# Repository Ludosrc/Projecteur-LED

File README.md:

# Projecteur-LED
Projet 1A Projecteur LED

Vous pouvez trouver dans le fichier Rapport Projecteur LED Asservi toute la conception du projecteur LED ainsi que les problèmes rencontrés.
À savoir que le projecteur n'est pas fonctionnel pour de multiples raisons qui sont détaillés dans le compte rendu.

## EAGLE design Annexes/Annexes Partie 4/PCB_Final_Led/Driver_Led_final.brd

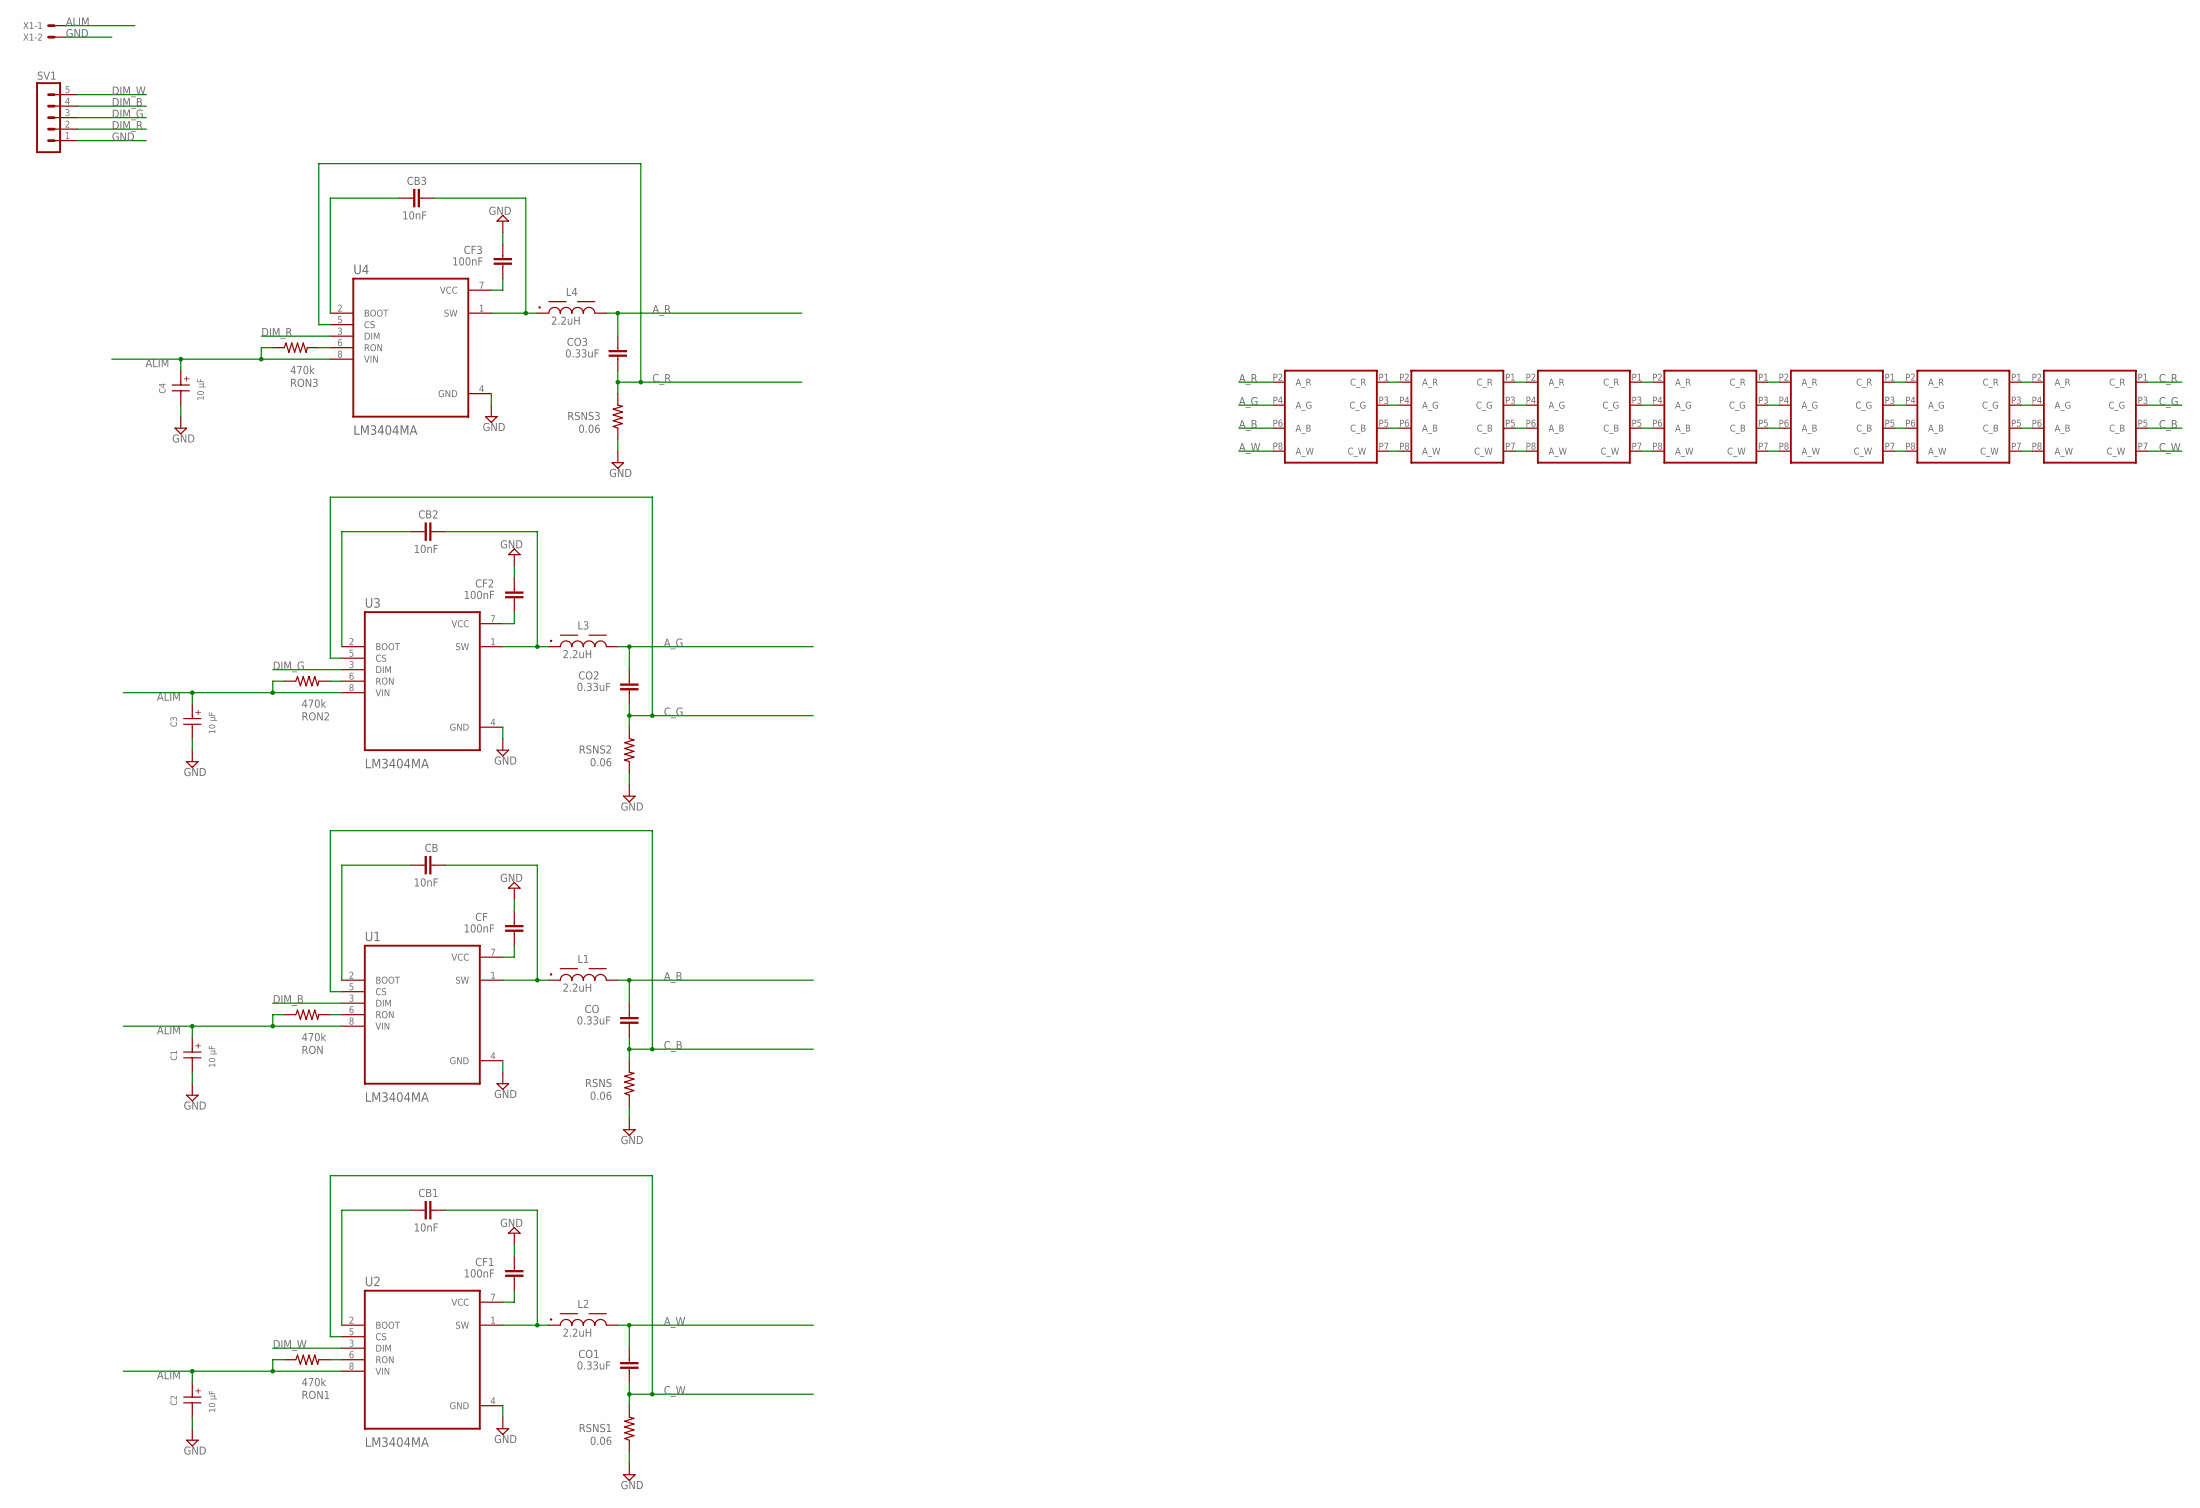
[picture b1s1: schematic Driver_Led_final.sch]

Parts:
C1, C2, C3, C4: 10 µF; WCAP-ASLL_4X5.5(DXL)
CB, CB1, CB2, CB3: 10nF; C0603
CF, CF1, CF2, CF3: 100nF; C0603
CO, CO1, CO2, CO3: 0.33uF; C0603
L1, L2, L3, L4: 2.2uH; WE-PDA_1260
RON, RON1, RON2, RON3: 470k; R0603
RSNS, RSNS1, RSNS2, RSNS3: 0.06; R0603
SV1: MA05-1
U1, U2, U3, U4: LM3404MA; SOIC127P599X175-8N
U$1, U$2, U$3, U$4, U$5, U$6, U$7: LE_RTDUW_S2WM_DEVICE; LE_RTDUW_S2WM_FOOTPRINT
X1: 22-23-2021

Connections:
ALIM: C1.1 (+), C2.1 (+), C3.1 (+), C4.1 (+), RON.1, RON1.1, RON2.1, RON3.1, U1.8 (VIN), U2.8 (VIN), U3.8 (VIN), U4.8 (VIN), X1.1
A_B: CO.2, L1.2, U$1.P6 (A_B)
A_G: CO2.2, L3.2, U$1.P4 (A_G)
A_R: CO3.2, L4.2, U$1.P2 (A_R)
A_W: CO1.2, L2.2, U$1.P8 (A_W)
C_B: CO.1, RSNS.2, U1.5 (CS), U$7.P5 (C_B)
C_G: CO2.1, RSNS2.2, U3.5 (CS), U$7.P3 (C_G)
C_R: CO3.1, RSNS3.2, U4.5 (CS), U$7.P1 (C_R)
C_W: CO1.1, RSNS1.2, U2.5 (CS), U$7.P7 (C_W)
DIM_B: SV1.4, U1.3 (DIM)
DIM_G: SV1.3, U3.3 (DIM)
DIM_R: SV1.2, U4.3 (DIM)
DIM_W: SV1.5, U2.3 (DIM)
GND: C1.2 (-), C2.2 (-), C3.2 (-), C4.2 (-), CF.1, CF1.1, CF2.1, CF3.1, RSNS.1, RSNS1.1, RSNS2.1, RSNS3.1, SV1.1, U1.4 (GND), U2.4 (GND), U3.4 (GND), U4.4 (GND), X1.2
unnamed: RON.2, U1.6 (RON)
unnamed: CB1.1, U2.2 (BOOT)
unnamed: CF.2, U1.7 (VCC)
unnamed: CB.1, U1.2 (BOOT)
unnamed: CB.2, L1.1, U1.1 (SW)
unnamed: CB1.2, L2.1, U2.1 (SW)
unnamed: CF1.2, U2.7 (VCC)
unnamed: RON1.2, U2.6 (RON)
unnamed: CB2.1, U3.2 (BOOT)
unnamed: CB2.2, L3.1, U3.1 (SW)
unnamed: CF2.2, U3.7 (VCC)
unnamed: RON2.2, U3.6 (RON)
unnamed: CB3.1, U4.2 (BOOT)
unnamed: CB3.2, L4.1, U4.1 (SW)
unnamed: CF3.2, U4.7 (VCC)
unnamed: RON3.2, U4.6 (RON)
unnamed: U$1.P1 (C_R), U$2.P2 (A_R)
unnamed: U$1.P3 (C_G), U$2.P4 (A_G)
unnamed: U$1.P5 (C_B), U$2.P6 (A_B)
unnamed: U$1.P7 (C_W), U$2.P8 (A_W)
unnamed: U$2.P1 (C_R), U$3.P2 (A_R)
unnamed: U$2.P3 (C_G), U$3.P4 (A_G)
unnamed: U$2.P5 (C_B), U$3.P6 (A_B)
unnamed: U$2.P7 (C_W), U$3.P8 (A_W)
unnamed: U$3.P7 (C_W), U$4.P8 (A_W)
unnamed: U$3.P5 (C_B), U$4.P6 (A_B)
unnamed: U$3.P3 (C_G), U$4.P4 (A_G)
unnamed: U$3.P1 (C_R), U$4.P2 (A_R)
unnamed: U$4.P1 (C_R), U$5.P2 (A_R)
unnamed: U$4.P3 (C_G), U$5.P4 (A_G)
unnamed: U$4.P5 (C_B), U$5.P6 (A_B)
unnamed: U$4.P7 (C_W), U$5.P8 (A_W)
unnamed: U$5.P1 (C_R), U$6.P2 (A_R)
unnamed: U$5.P3 (C_G), U$6.P4 (A_G)
unnamed: U$5.P5 (C_B), U$6.P6 (A_B)
unnamed: U$5.P7 (C_W), U$6.P8 (A_W)
unnamed: U$6.P1 (C_R), U$7.P2 (A_R)
unnamed: U$6.P3 (C_G), U$7.P4 (A_G)
unnamed: U$6.P5 (C_B), U$7.P6 (A_B)
unnamed: U$6.P7 (C_W), U$7.P8 (A_W)

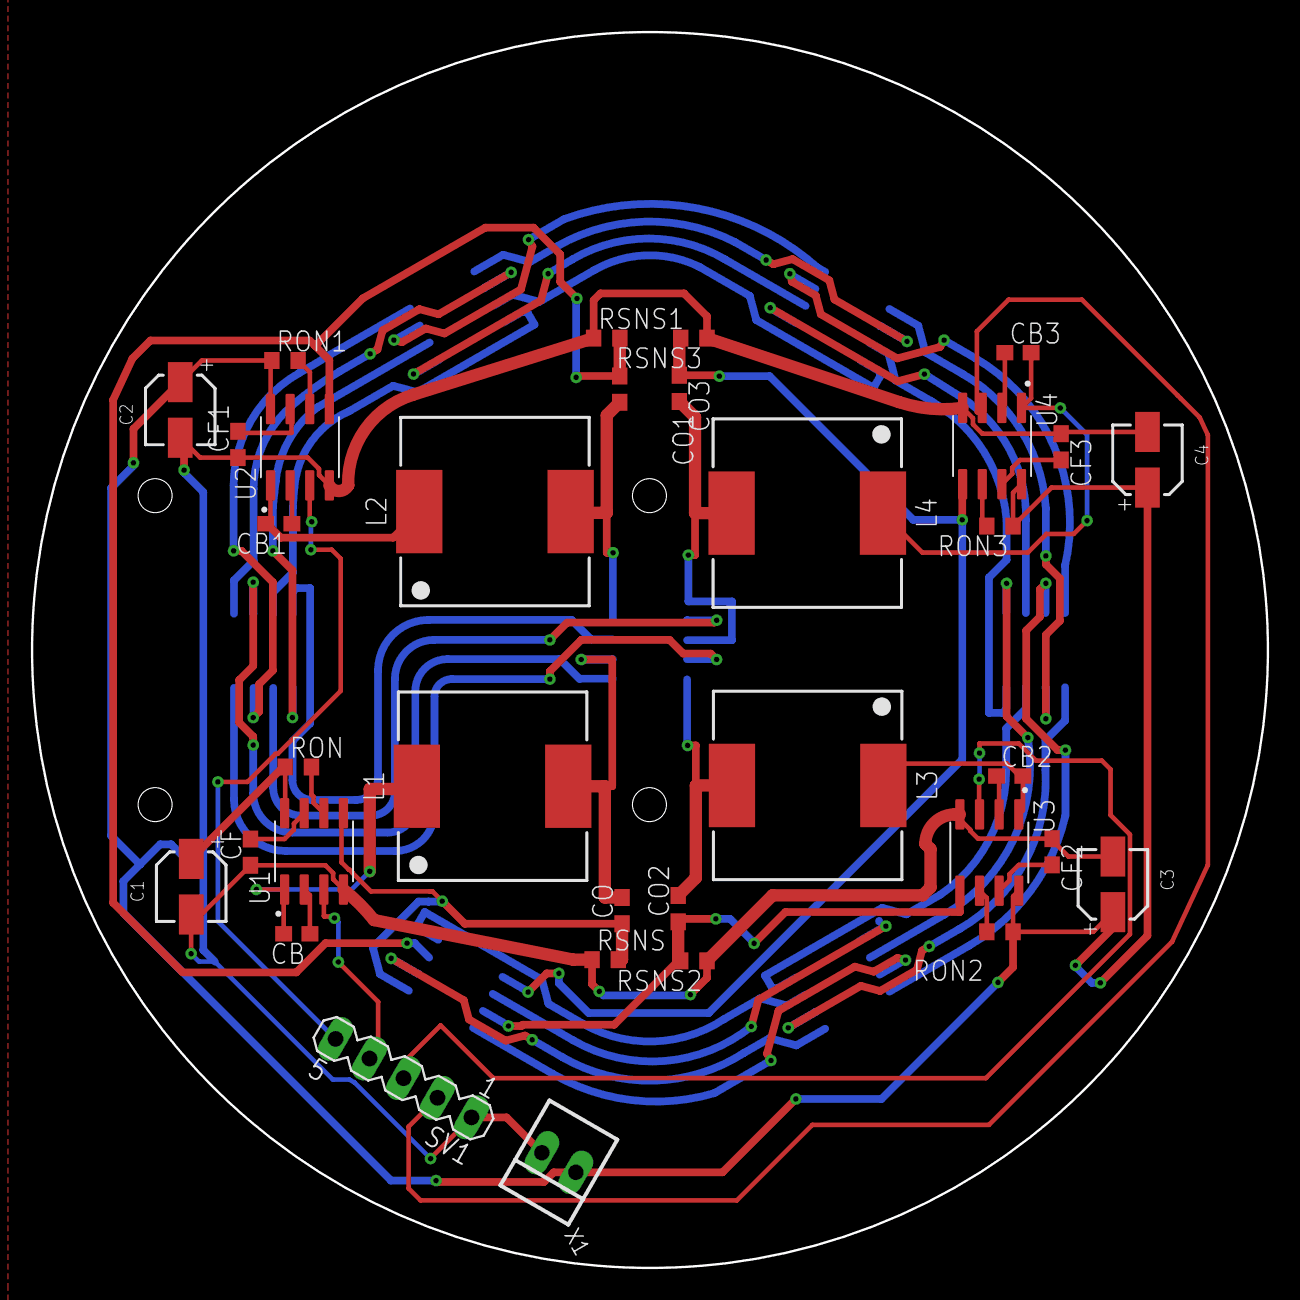
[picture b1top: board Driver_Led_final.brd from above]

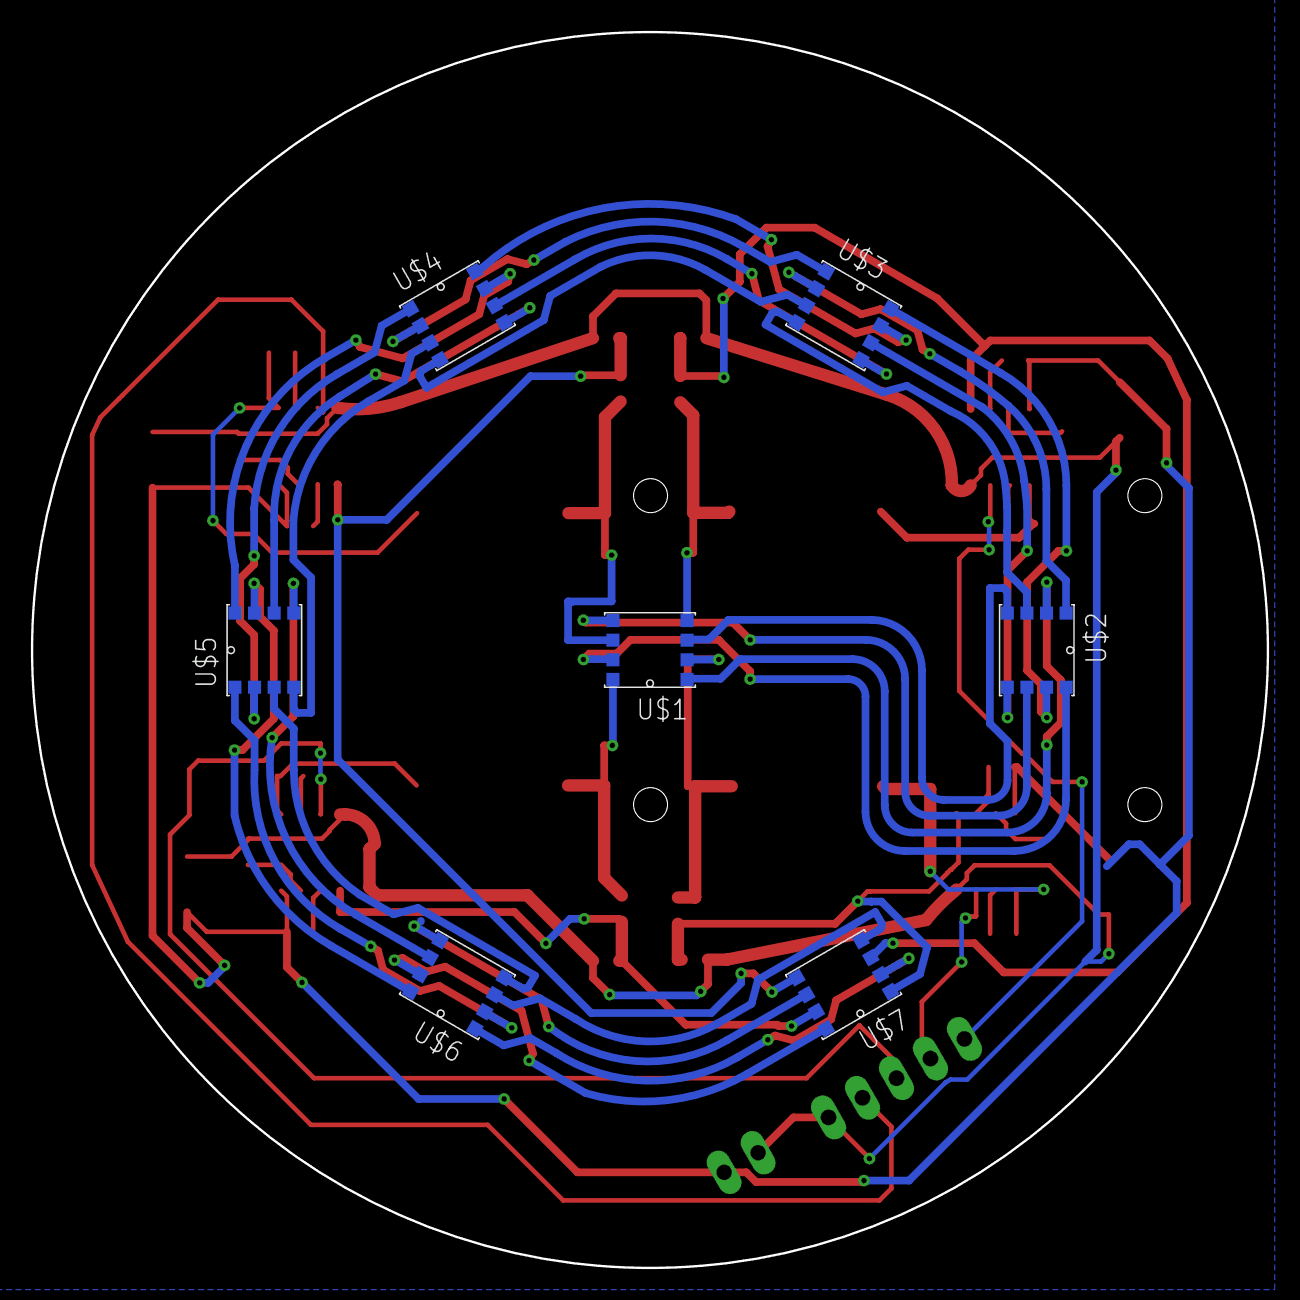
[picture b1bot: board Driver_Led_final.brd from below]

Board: 2 copper layers, 80.0 x 80.0 mm, 41 parts (7 on the bottom side), 54 nets.

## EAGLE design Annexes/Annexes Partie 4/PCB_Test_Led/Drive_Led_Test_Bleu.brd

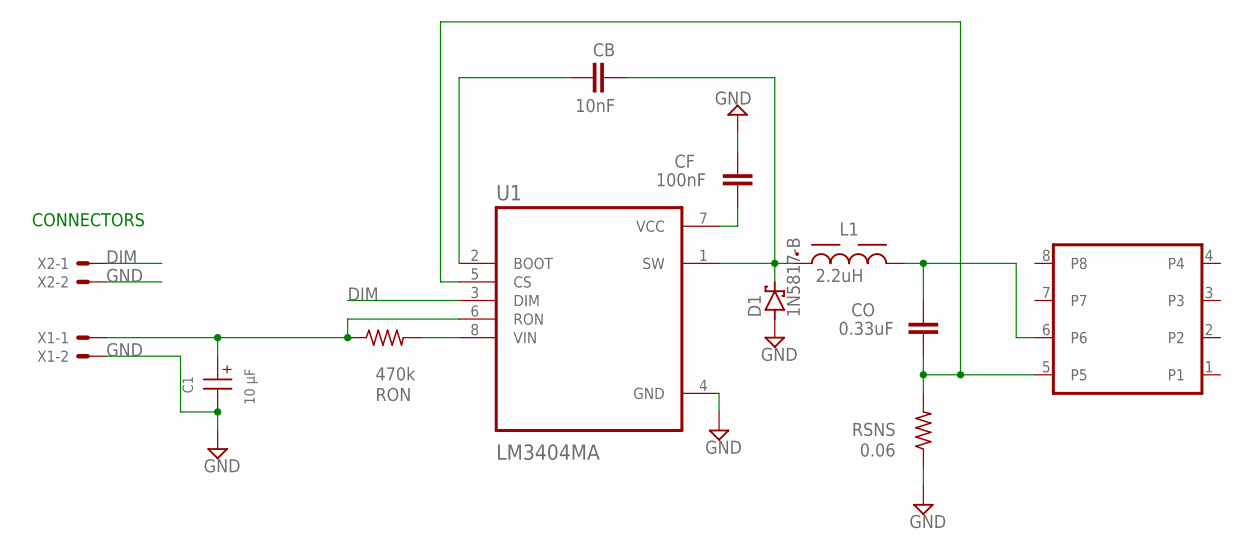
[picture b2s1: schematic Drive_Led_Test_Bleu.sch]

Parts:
C1: 10 µF; WCAP-ASLL_4X5.5(DXL)
CB: 10nF; C0603
CF: 100nF; C0603
CO: 0.33uF; C0603
D1: 1N5817-B; DO41-7.6
L1: 2.2uH; WE-PDA_1260
RON: 470k; R0603
RSNS: 0.06; R0603
U1: LM3404MA; SOIC127P599X175-8N
U$1: LE_RTDUW_S2WM_DEVICE; LE_RTDUW_S2WM_FOOTPRINT
X1, X2: 22-23-2021

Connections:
DIM: U1.3 (DIM), X2.1
GND: C1.2 (-), CF.1, D1.A, RSNS.1, U1.4 (GND), X1.2, X2.2
unnamed: RON.2, U1.8 (VIN)
unnamed: C1.1 (+), RON.1, U1.6 (RON), X1.1
unnamed: CF.2, U1.7 (VCC)
unnamed: CB.1, U1.2 (BOOT)
unnamed: CB.2, D1.C, L1.1, U1.1 (SW)
unnamed: CO.1, RSNS.2, U1.5 (CS), U$1.5
unnamed: CO.2, L1.2, U$1.6
P1: U$1.1
P2: U$1.2

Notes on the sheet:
CONNECTORS

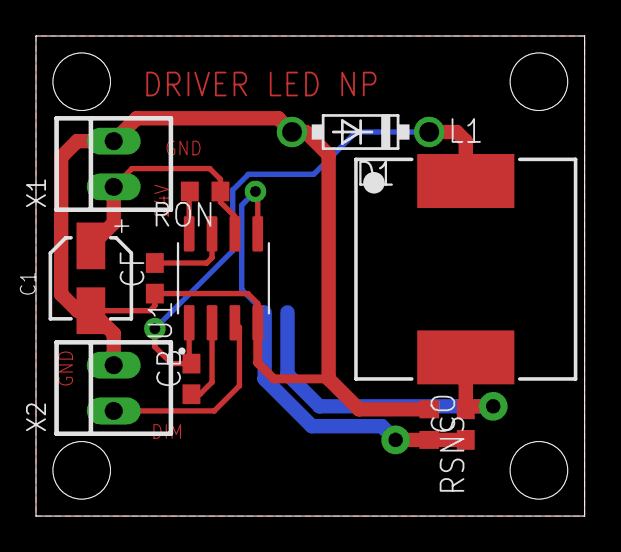
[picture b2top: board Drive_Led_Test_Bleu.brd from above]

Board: 2 copper layers, 30.5 x 26.7 mm, 12 parts (1 on the bottom side), 9 nets.

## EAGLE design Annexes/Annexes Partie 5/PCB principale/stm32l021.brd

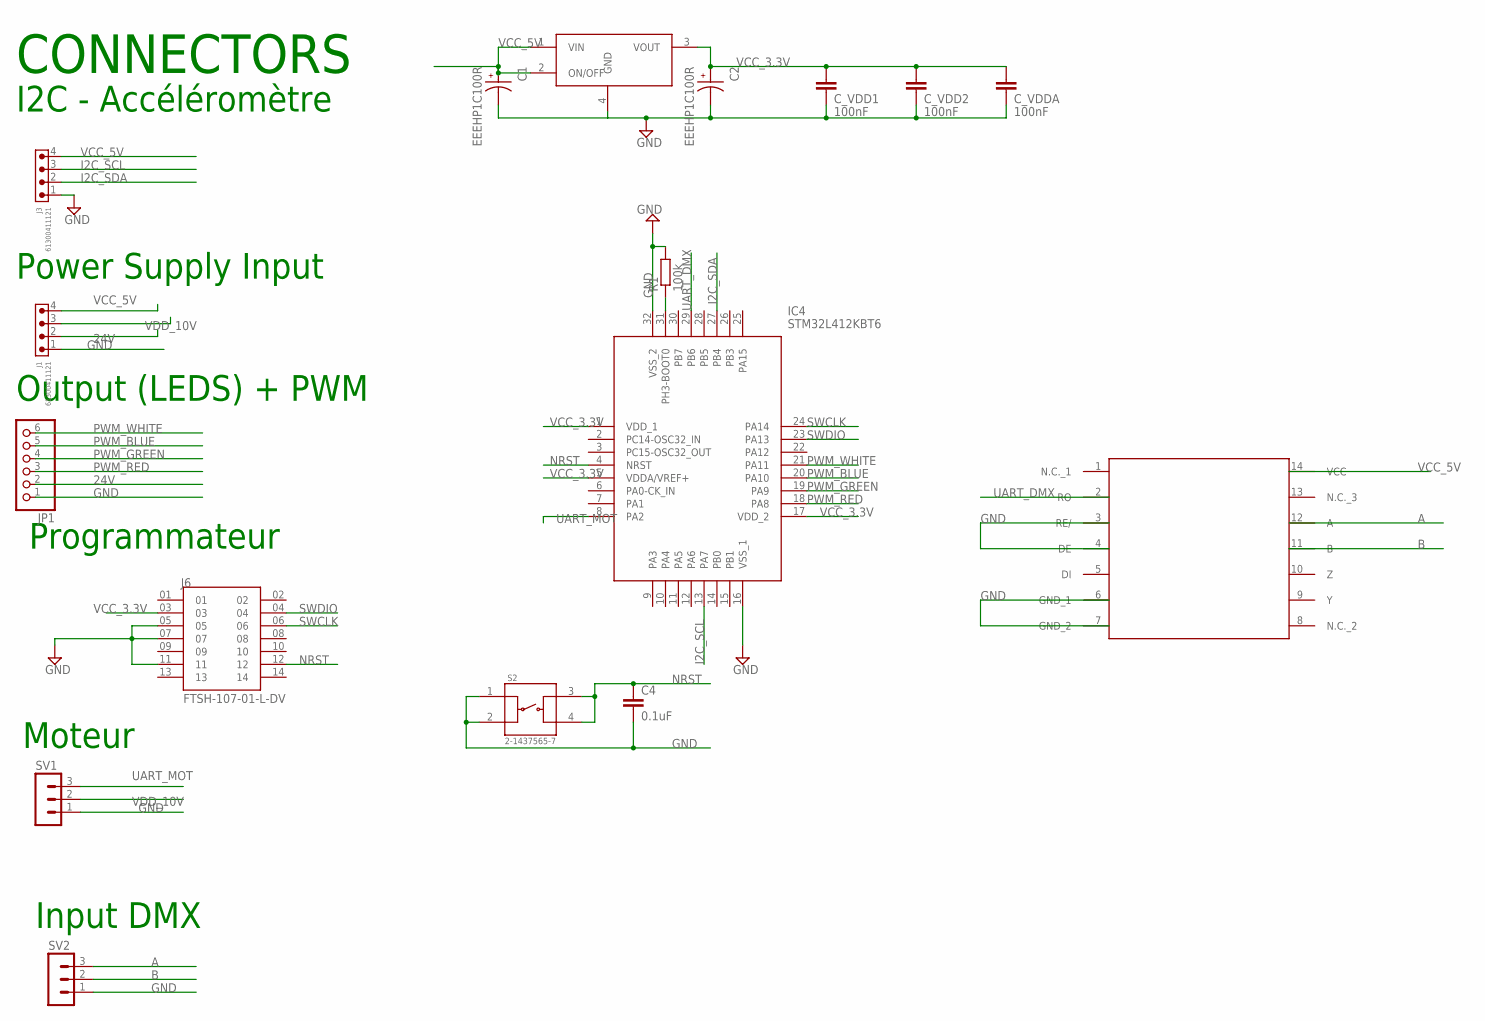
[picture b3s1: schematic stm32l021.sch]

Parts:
C1, C2: EEEHP1C100R; CAP_EEEHP1C100R
C4: 0.1uF; C0603
C_VDD1, C_VDD2: 100nF; C0603
C_VDDA: 100nF; C0603
IC4: STM32L412KBT6; QFP80P900X900X160-32N
J1, J3: 61300411121
J6: FTSH-107-01-L-DV; SAMTEC_FTSH-107-01-L-DV
JP1: PINHD-1X6; 1X06
R1: 100k; R0603
S2: 2-1437565-7; SW_2-1437565-7
SV1, SV2: MA03-1
U1: SOIC127P600X175-14N
U$1: NCV33375ST3.3T3G; VREG_NCP1117STAT3G

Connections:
24V: J1.2, JP1.2
A: SV2.3, U1.12 (A)
B: SV2.2, U1.11 (B)
GND: C1.2, C2.2, C4.2, C_VDD1.2, C_VDD2.2, C_VDDA.2, IC4.16 (VSS_1), IC4.32 (VSS_2), J1.1, J3.1, J6.05, J6.07, J6.11, JP1.1, R1.2, S2.1, S2.2, SV1.1, SV2.1, U1.3 (RE/), U1.4 (DE), U1.6 (GND_1), U1.7 (GND_2), U$1.4 (GND)
I2C_SCL: IC4.13 (PA7), J3.3
I2C_SDA: IC4.27 (PB4), J3.2
unnamed: IC4.31 (PH3-BOOT0), R1.1
NRST: C4.1, IC4.4 (NRST), J6.12, S2.3, S2.4
PWM_BLUE: IC4.20 (PA10), JP1.5
PWM_GREEN: IC4.19 (PA9), JP1.4
PWM_RED: IC4.18 (PA8), JP1.3
PWM_WHITE: IC4.21 (PA11), JP1.6
SWCLK: IC4.24 (PA14), J6.06
SWDIO: IC4.23 (PA13), J6.04
UART_DMX: IC4.29 (PB6), U1.2 (RO)
UART_MOT: IC4.8 (PA2), SV1.3
VCC_3.3V: C2.1, C_VDD1.1, C_VDD2.1, C_VDDA.1, IC4.1 (VDD_1), IC4.5 (VDDA/VREF+), IC4.17 (VDD_2), J6.03, U$1.3 (VOUT)
VCC_5V: C1.1, J1.4, J3.4, U1.14 (VCC), U$1.1 (VIN), U$1.2 (ON/OFF)
VDD_10V: J1.3, SV1.2

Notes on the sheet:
CONNECTORS
I2C - Accéléromètre
Power Supply Input
Programmateur
Output (LEDS) + PWM
Moteur
Input DMX

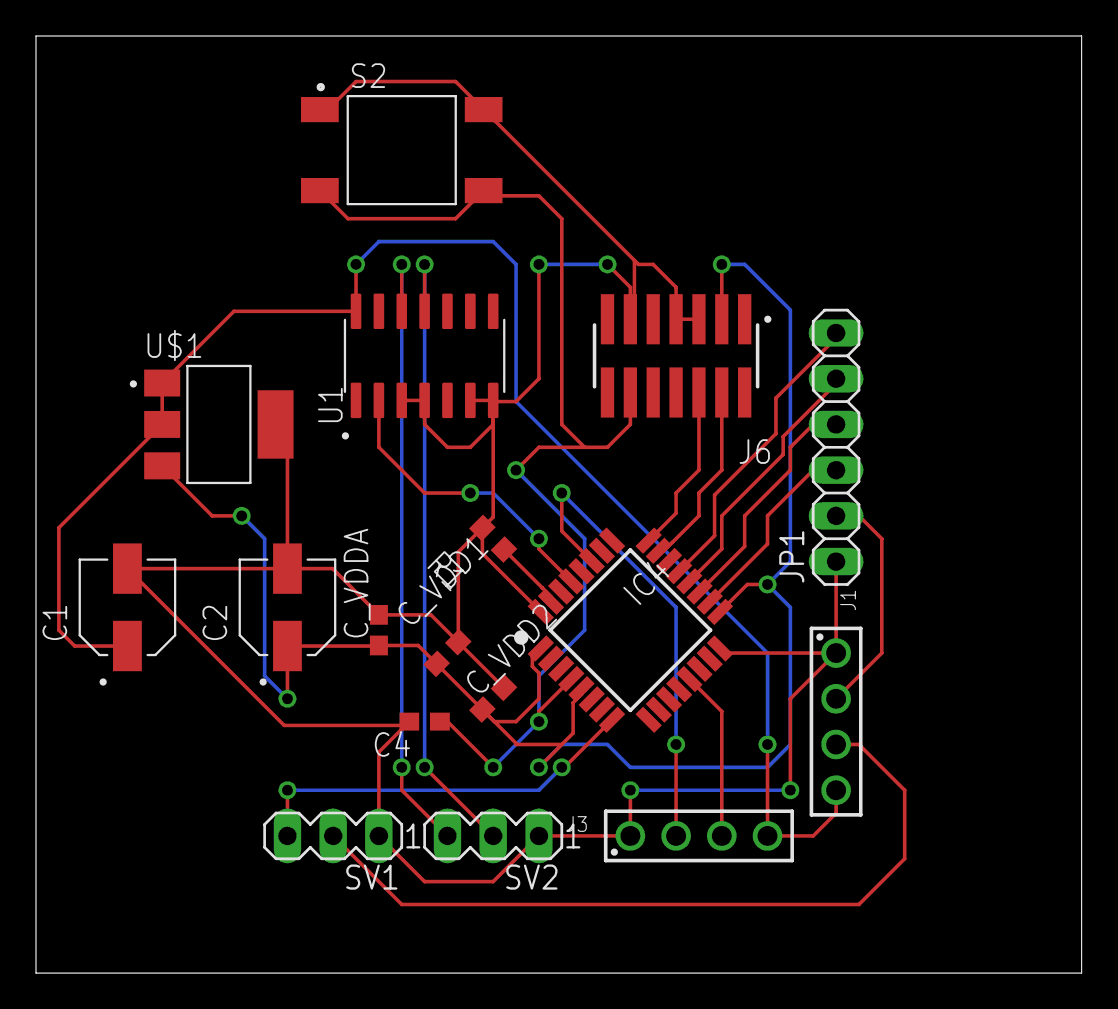
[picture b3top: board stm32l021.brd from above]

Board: 2 copper layers, 58.1 x 52.1 mm, 17 parts (0 on the bottom side), 19 nets.

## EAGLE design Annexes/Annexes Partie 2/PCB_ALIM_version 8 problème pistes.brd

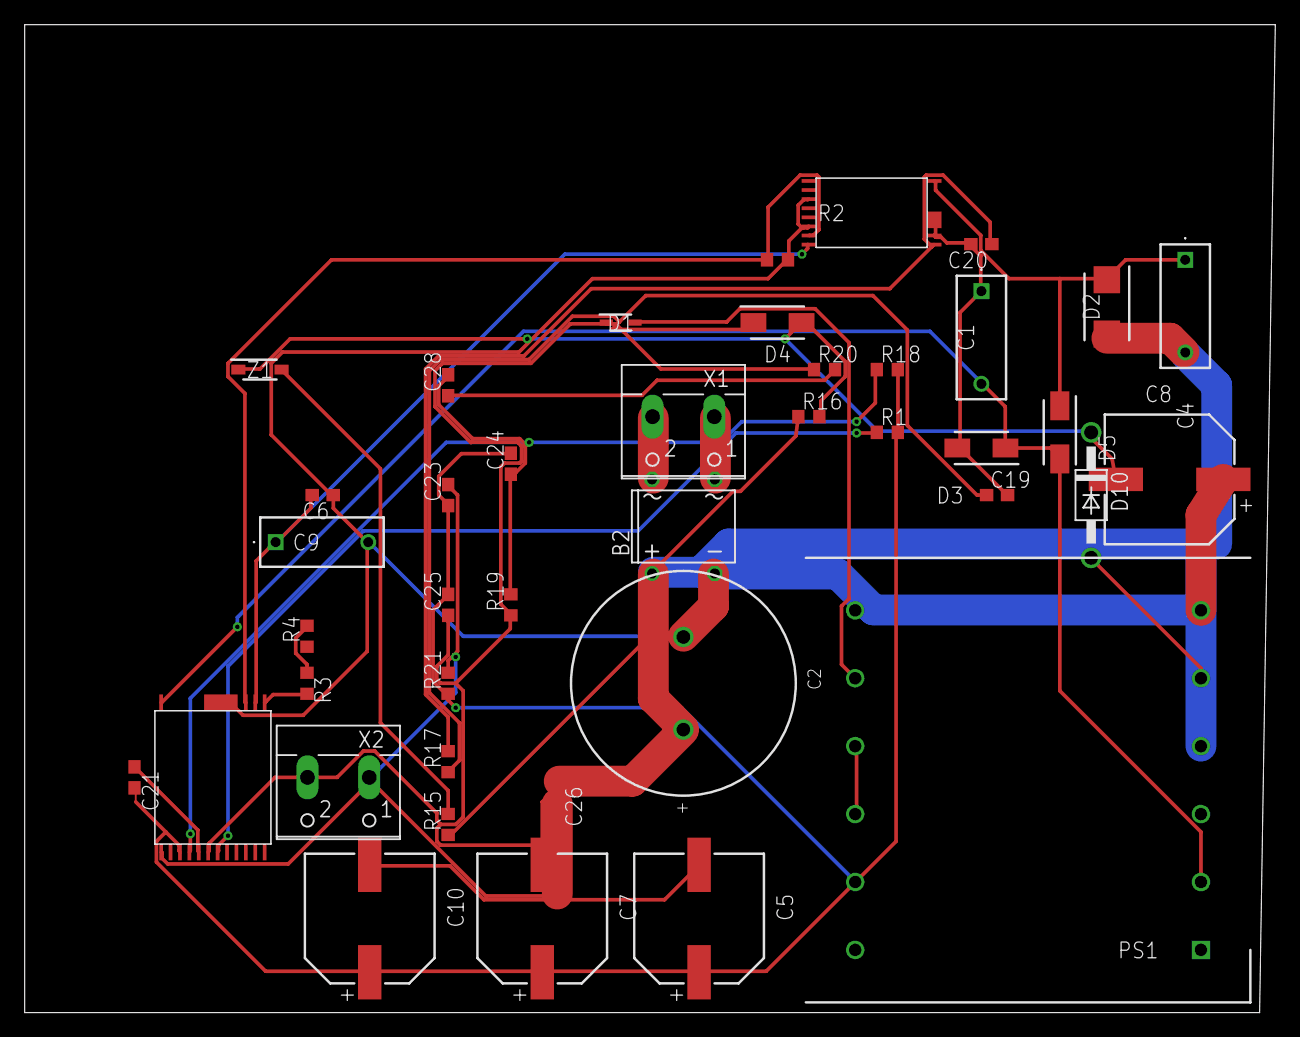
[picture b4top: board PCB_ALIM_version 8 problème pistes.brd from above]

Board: 2 copper layers, 101.3 x 80.0 mm, 41 parts (0 on the bottom side), 26 nets.

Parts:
B2: DBDB104G; DB
C1, C4, C9: MKP1J012202C00KSSD
C2: 120 µF; WCAP-ATG8_18X41X7.5(DXL)
C5, C7, C8, C10: 220 µF; WCAP-ASLI_10X10.5(DXL)
C6: 4.7uF, 50V; C0603
C19: 1uF, 100V; C0603
C20: 100nF, 50V; C0603
C21: 2.2uF, 25V; C0603
C23: 1uF, 25V; C0603
C24: 330pF, 50V; C0603
C25: 1uF, 50V; C0603
C26: 220pF, 250VAC; C0603
C28: 6.8n, 50V; C0603
D1: BAV21WS-7-F; SOD2513X120N
D2: SMBJ200A; DIOM5436X261N
D3, D4: US1M-13-F; SODFL5226X240N
D5: US1K-13-F; DIOM5226X240N
D10: 1N4933; DO41-10
PS1: 760895441; DIPS2800W80P550L3600H2600Q12N
R1: 47, 1/10W; R0603
R2: 30k; R0603
R3, R4: 2M; R0603
R15: 47; R0603
R16: 2k; R0603
R17: 3.09k; R0603
R18, R20: 10k; R0603
R19: 150k, 1/8W; R0603
R21: 0.009; R0603
U$3: CLAMPZERO; MINSOP-16A
U$4: INNOSWITCH4-CZ; INSOP-24D
X1, X2: W237-102
Z1: MMSZ5243BT1G; SOD3716X135N

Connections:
BPP: C6.2, C9.1, U$3.P$8, U$4.P$14
BPS: C21.1, U$4.P$5
DRAIN: C1.2, D3.1, D5.2, PS1.2, U$4.P$24
FB: C24.1, C28.2, R18.1, R19.2, U$4.P$4
FL3: C5.1, C7.1, C10.1, C21.2, C23.1, C24.2, C25.2, PS1.11, R1.2, R18.2, R21.1, U$4.P$3
FW: R1.1, U$4.P$7
GND: B2.-, C2.2, C6.1, C8.1, C9.2, PS1.6, R2.2, U$3.P$3, U$3.P$6, U$4.P$16
HSD: R2.1, U$3.P$7, U$4.P$15
L: B2.AC1, X1.1
N: B2.AC2, X1.2
unnamed: C8.2, D4.2, D10.C, R16.2, Z1.1
unnamed: R15.2, Z1.2
unnamed: PS1.9, PS1.10
unnamed: C28.1, R20.2
unnamed: R3.2, U$4.P$13
unnamed: R3.1, R4.2
unnamed: C1.1, C19.2, C20.2, D3.2, U$3.P$10, U$3.P$11
unnamed: C19.1, D4.1, R17.1
unnamed: C20.1, R17.2, U$3.P$9
unnamed: D10.A, PS1.5
unnamed: C4.1, D2.1, D5.1, U$3.P$16
unnamed: R15.1, R16.1
unnamed: D1.2, PS1.8
RTN: C23.2, C26.2, R21.2, U$4.P$1, X2.1
VCC_330V: B2.+, C2.1, C4.2, C26.1, D2.2, PS1.4
VOUT: C5.2, C7.2, C10.2, C25.1, D1.1, R19.1, R20.1, U$4.P$6, X2.2

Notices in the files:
parts and their libraries:
Eagle_WCAP-ASLI: Copyright: Würth Elektronik
